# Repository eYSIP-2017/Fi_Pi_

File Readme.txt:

Hello,
This repo contains the documentation and codes of the project 
FiPi- Adapter board development for Firebird V using Raspberry Pi

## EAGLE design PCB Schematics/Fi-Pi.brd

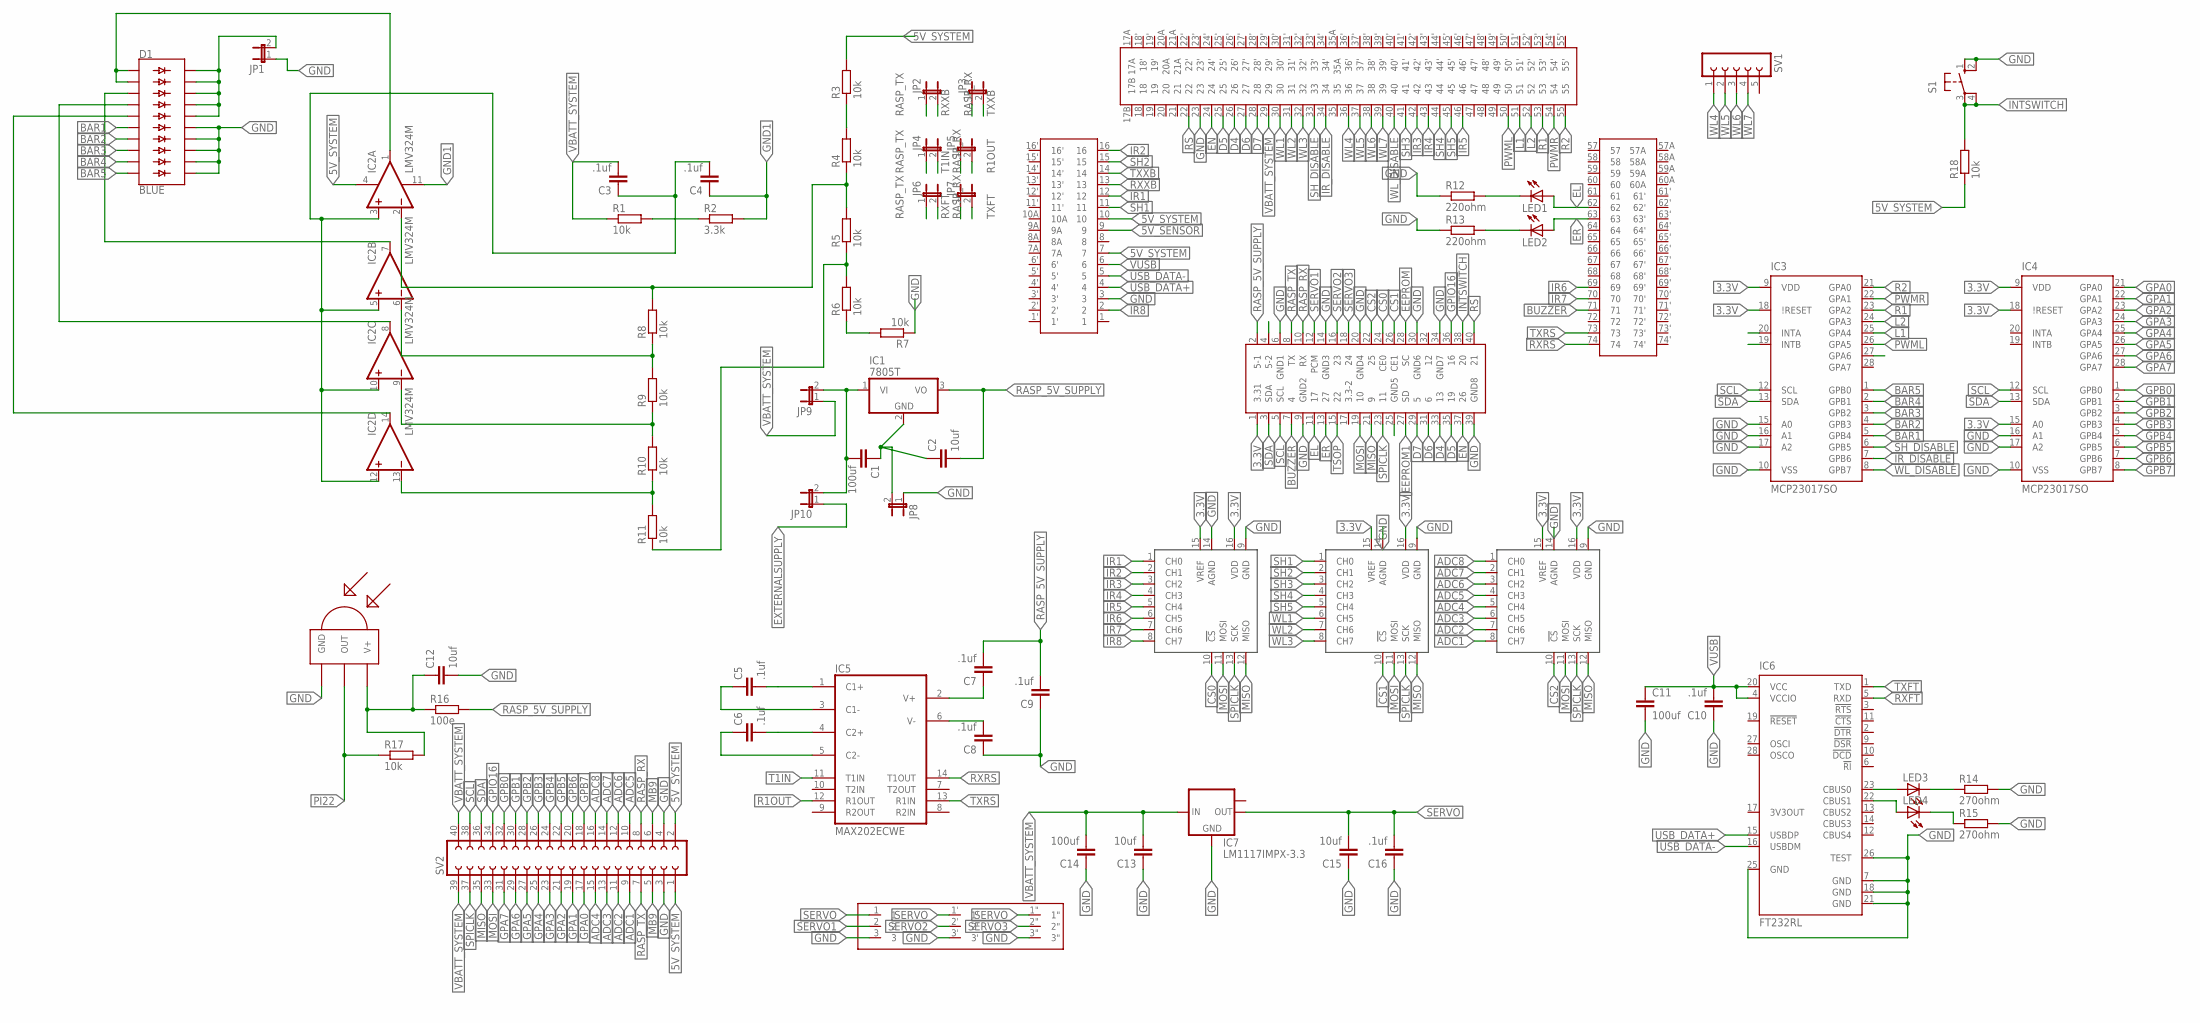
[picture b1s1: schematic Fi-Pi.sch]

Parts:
C1, C11, C14: 100uf; C1206
C2, C12, C13, C15: 10uf; C1206
C3, C4, C5, C6, C7, C8, C9, C10, C16: .1uf; C1206
D1: BLUE; LED_BARGRAPH_10
IC1: 7805T; TO220H
IC2: LMV324M; SO14
IC3, IC4: MCP23017SO; SO28W
IC5: MAX202ECWE; SO16L
IC6: FT232RL; SSOP28
IC7: LM1117IMPX-3.3; SOT223
JP1, JP2, JP3, JP4, JP5, JP6, JP7, JP8, JP9, JP10: JP1E; JP1
LED1, LED2, LED3, LED4: LED_E; LED_1206
R1, R3, R4, R5, R6, R7, R8, R9, R10, R11, R17, R18: 10k; R1206
R2: 3.3k; R1206
R12, R13: 220ohm; R1206
R14, R15: 270ohm; R1206
R16: 100e; R1206
S1: 10-XX; B3F-10XX
SV1: FE05-1
SV2: FE20-2
U$1: DAUGHTERBOARDDAUGHTERBOARD; DAUGHTERBOARD
U$2: MALE_HEADER; MALE_HEADER_PACKAGE
U$3, U$4, U$5: MCP3008SL; SO16
U$6: TSOP1738; TSOP17XX
U$7: SERVO

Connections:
3.3V: IC3.9 (VDD), IC3.18 (\!RESET), IC4.9 (VDD), IC4.15 (A0), IC4.18 (\!RESET), U$2.1 (3.31), U$3.15 (VREF), U$3.16 (VDD), U$4.15 (VREF), U$4.16 (VDD), U$5.15 (VREF), U$5.16 (VDD)
5V_SENSOR: U$1.9
5V_SYSTEM: IC2.4 (V+), R3.2, R18.1, SV2.1, SV2.2, U$1.7, U$1.10
A: D1.16 (C4), D1.17 (C3), D1.18 (C2), D1.19 (C1), D1.20 (C), JP1.2
ADC1: SV2.9, U$5.8 (CH7)
ADC2: SV2.11, U$5.7 (CH6)
ADC3: SV2.13, U$5.6 (CH5)
ADC4: SV2.15, U$5.5 (CH4)
ADC5: SV2.10, U$5.4 (CH3)
ADC6: SV2.12, U$5.3 (CH2)
ADC7: SV2.14, U$5.2 (CH1)
ADC8: SV2.16, U$5.1 (CH0)
BAR1: D1.6 (A5), IC3.5 (GPB4)
BAR2: D1.7 (A6), IC3.4 (GPB3)
BAR3: D1.8 (A7), IC3.3 (GPB2)
BAR4: D1.9 (A8), IC3.2 (GPB1)
BAR5: D1.10 (A9), IC3.1 (GPB0)
BUZZER: U$1.71, U$2.7 (4)
CS0: U$2.24 (CE0), U$3.10 (!CS)
CS1: U$2.26 (CE1), U$4.10 (!CS)
CS2: U$2.22 (25), U$5.10 (!CS)
D4: U$1.26, U$2.33 (13)
D5: U$1.25, U$2.35 (19)
D6: U$1.27, U$2.31 (6)
D7: U$1.28, U$2.29 (5)
EEPROM: U$2.28 (SC)
EEPROM1: U$2.27 (SD)
EL: LED1.A, U$1.62, U$2.11 (17)
EN: U$1.24, U$2.37 (26)
ER: LED2.A, U$1.63, U$2.13 (27)
EXTERNALSUPPLY: JP10.1
GND: C8.1, C9.1, C10.1, C11.2, C12.2, C13.1, C14.1, C15.1, C16.1, D1.11 (C9), D1.12 (C8), D1.13 (C7), D1.14 (C6), D1.15 (C5), IC3.10 (VSS), IC3.15 (A0), IC3.16 (A1), IC3.17 (A2), IC4.10 (VSS), IC4.16 (A1), IC4.17 (A2), IC5.15 (GND), IC6.7 (GND), IC6.18 (GND), IC6.21 (GND), IC6.25 (GND), IC6.26 (TEST), IC7.1 (GND), JP1.1, JP8.1, R7.1, R12.1, R13.1, R14.2, R15.2, S1.1 (S), S1.2 (S1), SV2.3, SV2.4, U$1.3, U$1.23, U$2.6 (GND1), U$2.9 (GND2), U$2.14 (GND3), U$2.20 (GND4), U$2.25 (GND5), U$2.30 (GND6), U$2.34 (GND7), U$2.39 (GND8), U$3.9 (GND), U$3.14 (AGND), U$4.9 (GND), U$4.14 (AGND), U$5.9 (GND), U$5.14 (AGND), U$6.GND, U$7.3, U$7.3", U$7.3'
GND1: C4.1, IC2.11 (V-), R2.2
GPA0: IC4.21 (GPA0), SV2.17
GPA1: IC4.22 (GPA1), SV2.19
GPA2: IC4.23 (GPA2), SV2.21
GPA3: IC4.24 (GPA3), SV2.23
GPA4: IC4.25 (GPA4), SV2.25
GPA5: IC4.26 (GPA5), SV2.27
GPA6: IC4.27 (GPA6), SV2.29
GPA7: IC4.28 (GPA7), SV2.31
GPB0: IC4.1 (GPB0), SV2.32
GPB1: IC4.2 (GPB1), SV2.30
GPB2: IC4.3 (GPB2), SV2.28
GPB3: IC4.4 (GPB3), SV2.26
GPB4: IC4.5 (GPB4), SV2.24
GPB5: IC4.6 (GPB5), SV2.22
GPB6: IC4.7 (GPB6), SV2.20
GPB7: IC4.8 (GPB7), SV2.18
GPIO16: SV2.34, U$2.36 (16)
INTSWITCH: R18.2, S1.3, S1.4 (P1), U$2.38 (20)
IR1: U$1.12, U$3.1 (CH0)
IR2: U$1.16, U$3.2 (CH1)
IR3: U$1.42, U$3.3 (CH2)
IR4: U$1.43, U$3.4 (CH3)
IR5: U$1.46, U$3.5 (CH4)
IR6: U$1.69, U$3.6 (CH5)
IR7: U$1.70, U$3.7 (CH6)
IR8: U$1.2, U$3.8 (CH7)
IR_DISABLE: IC3.7 (GPB6), U$1.34
L1: IC3.25 (GPA4), U$1.51
L2: IC3.24 (GPA3), U$1.52
MB9: SV2.5, SV2.6
MISO: SV2.35, U$2.21 (9), U$3.12 (MISO), U$4.12 (MISO), U$5.12 (MISO)
MOSI: SV2.33, U$2.19 (10), U$3.11 (MOSI), U$4.11 (MOSI), U$5.11 (MOSI)
unnamed: C1.1, C2.1, IC1.2 (GND), JP8.2
unnamed: R5.1, R6.2, R11.1
unnamed: C3.1, C4.2, IC2.3 (+IN), IC2.5 (+IN), IC2.10 (+IN), IC2.12 (+IN), R1.2, R2.1
unnamed: R3.1, R4.2
unnamed: IC2.2 (-IN), R4.1, R5.2, R8.2
unnamed: IC2.6 (-IN), R8.1, R9.2
unnamed: R6.1, R7.2
unnamed: IC2.9 (-IN), R9.1, R10.2
unnamed: IC2.13 (-IN), R10.1, R11.2
unnamed: D1.1 (A), D1.2 (A1), IC2.1 (OUT)
unnamed: C5.1, IC5.3 (C1-)
unnamed: D1.4 (A3), IC2.8 (OUT)
unnamed: D1.5 (A4), IC2.14 (OUT)
unnamed: LED1.C, R12.2
unnamed: LED2.C, R13.2
unnamed: C5.2, IC5.1 (C1+)
unnamed: C6.2, IC5.4 (C2+)
unnamed: C6.1, IC5.5 (C2-)
unnamed: LED4.C, R15.1
unnamed: D1.3 (A2), IC2.7 (OUT)
unnamed: LED3.C, R14.1
unnamed: IC6.23 (CBUS0), LED3.A
unnamed: IC6.22 (CBUS1), LED4.A
unnamed: C7.1, IC5.2 (V+)
unnamed: C8.2, IC5.6 (V-)
unnamed: C12.1, R16.1, R17.2, U$6.V+
PI4: U$2.4 (5-2)
PI22: R17.1, U$6.OUT
PWML: IC3.26 (GPA5), U$1.50
PWMR: IC3.22 (GPA1), U$1.54
R1: IC3.23 (GPA2), U$1.53
R1OUT: IC5.12 (R1OUT), JP5.2
R2: IC3.21 (GPA0), U$1.55
RASP_5V_SUPPLY: C2.2, C7.2, C9.2, IC1.3 (VO), R16.2, U$2.2 (5-1)
RASP_RX: JP3.1, JP5.1, JP7.1, SV2.8, U$2.10 (RX)
RASP_TX: JP2.1, JP4.1, JP6.1, SV2.7, U$2.8 (TX)
RS: U$1.22, U$2.40 (21)
RXFT: IC6.5 (RXD), JP6.2
RXRS: IC5.14 (T1OUT), U$1.74
RXXB: JP2.2, U$1.13
SCL: IC3.12 (SCL), IC4.12 (SCL), SV2.38, U$2.5 (SCL)
SDA: IC3.13 (SDA), IC4.13 (SDA), SV2.36, U$2.3 (SDA)
SERVO: C15.2, C16.2, IC7.2 (OUT), U$7.1, U$7.1", U$7.1'
SERVO1: U$2.12 (PCM), U$7.2
SERVO2: U$2.16 (23), U$7.2'
SERVO3: U$2.18 (24), U$7.2"
SH1: U$1.11, U$4.1 (CH0)
SH2: U$1.15, U$4.2 (CH1)
SH3: U$1.41, U$4.3 (CH2)
SH4: U$1.44, U$4.4 (CH3)
SH5: U$1.45, U$4.5 (CH4)
SH_DISABLE: IC3.6 (GPB5), U$1.33
SPICLK: SV2.37, U$2.23 (11), U$3.13 (SCK), U$4.13 (SCK), U$5.13 (SCK)
T1IN: IC5.11 (T1IN), JP4.2
TSOP: U$2.15 (22)
TXFT: IC6.1 (TXD), JP7.2
TXRS: IC5.13 (R1IN), U$1.73
TXXB: JP3.2, U$1.14
USB_DATA+: IC6.15 (USBDP), U$1.4
USB_DATA-: IC6.16 (USBDM), U$1.5
VBATT_SYSTEM: C1.2, C3.2, C13.2, C14.2, IC1.1 (VI), IC7.3 (IN), JP9.1, JP9.2, JP10.2, R1.1, SV2.39, SV2.40, U$1.29
VCC: IC5.16 (VCC)
VUSB: C10.2, C11.1, IC6.4 (VCCIO), IC6.20 (VCC), U$1.6
WL1: U$1.30, U$4.6 (CH5)
WL2: U$1.31, U$4.7 (CH6)
WL3: U$1.32, U$4.8 (CH7)
WL4: SV1.1, U$1.36
WL5: SV1.2, U$1.37
WL6: SV1.3, U$1.38
WL7: SV1.4, U$1.39
WL_DISABLE: IC3.8 (GPB7), U$1.40

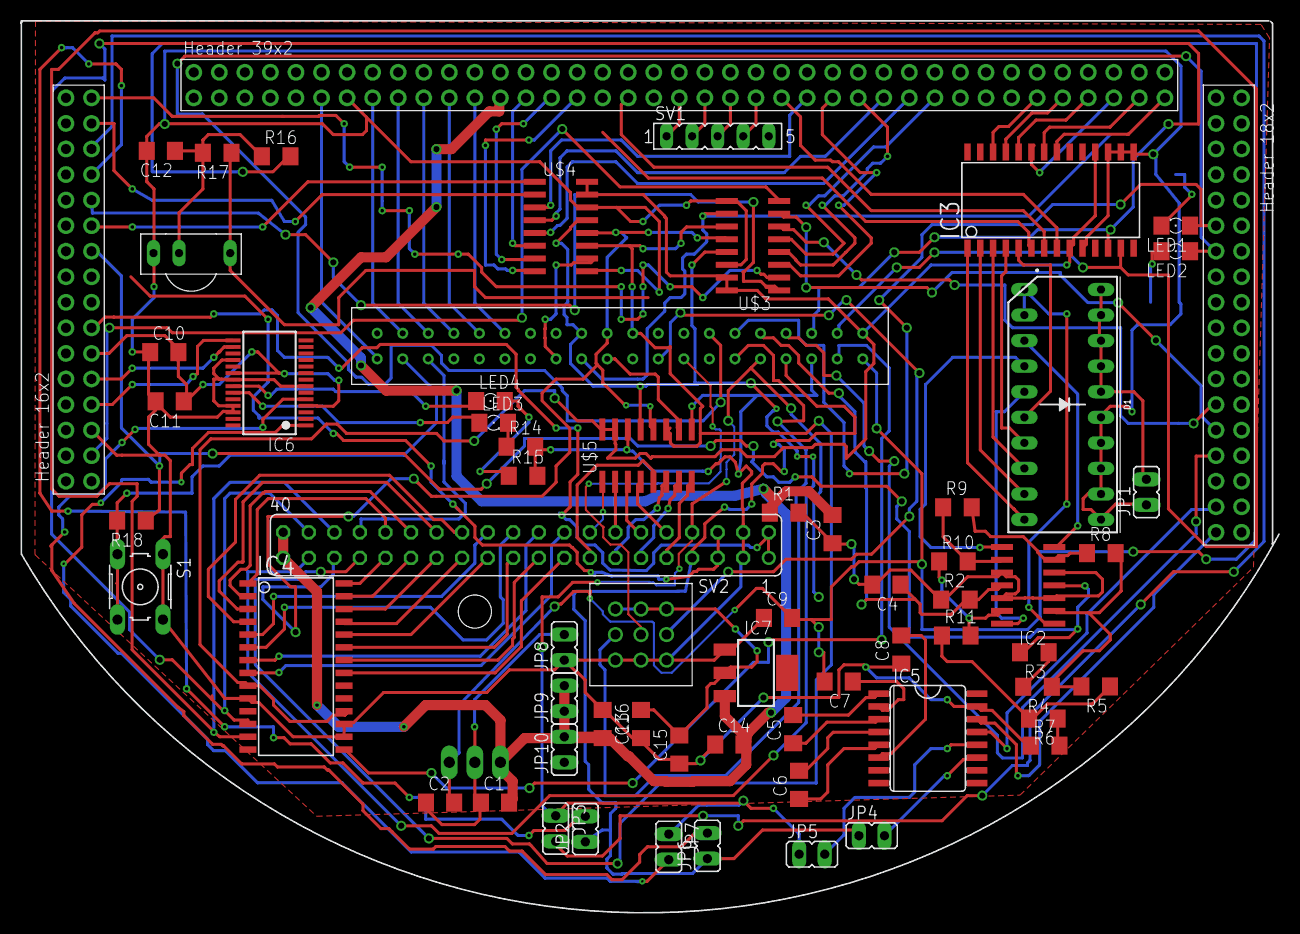
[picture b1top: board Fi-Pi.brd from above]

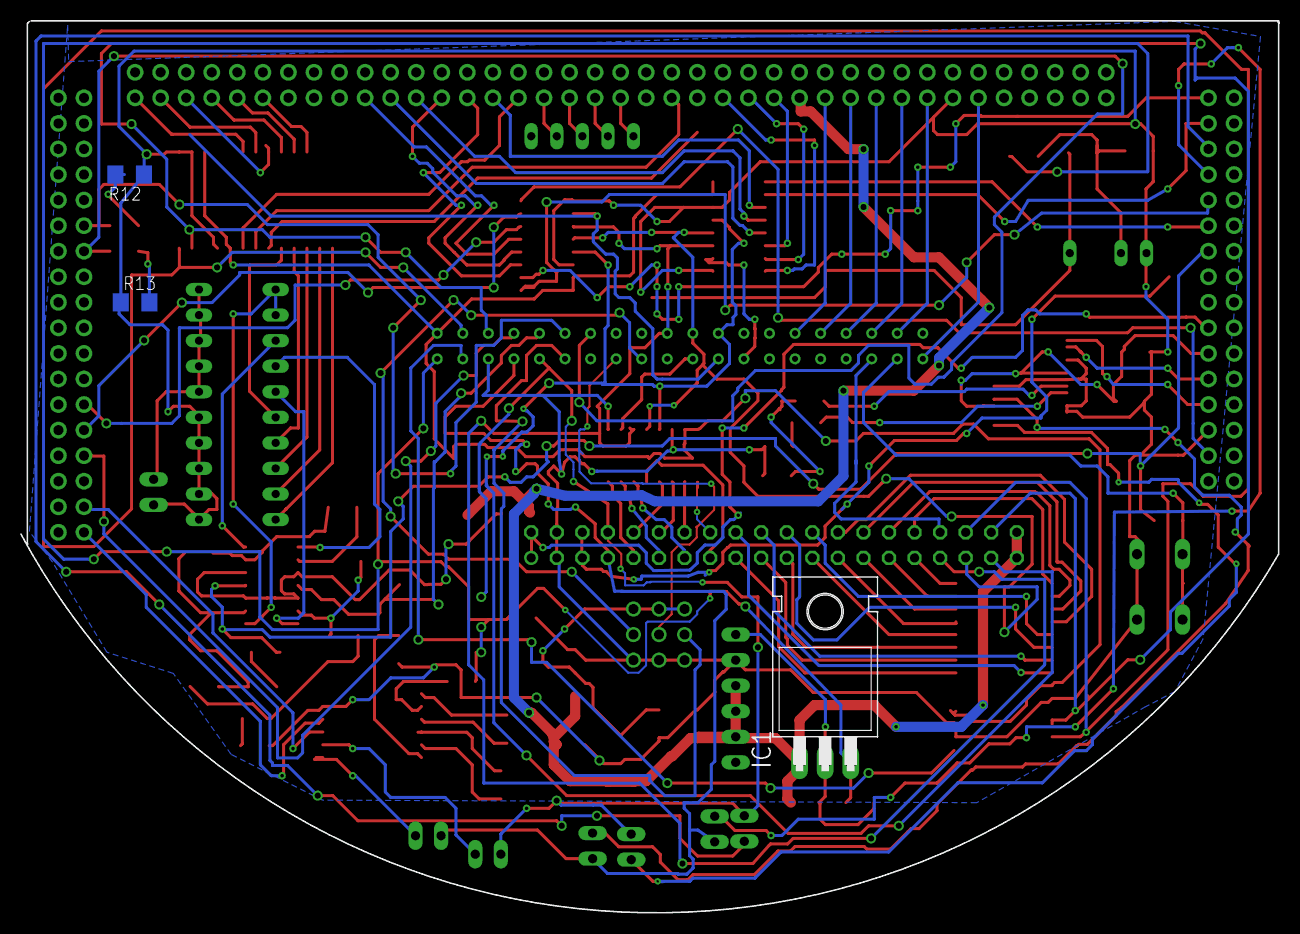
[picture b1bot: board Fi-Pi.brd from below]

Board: 2 copper layers, 125.1 x 88.6 mm, 66 parts (3 on the bottom side), 129 nets.

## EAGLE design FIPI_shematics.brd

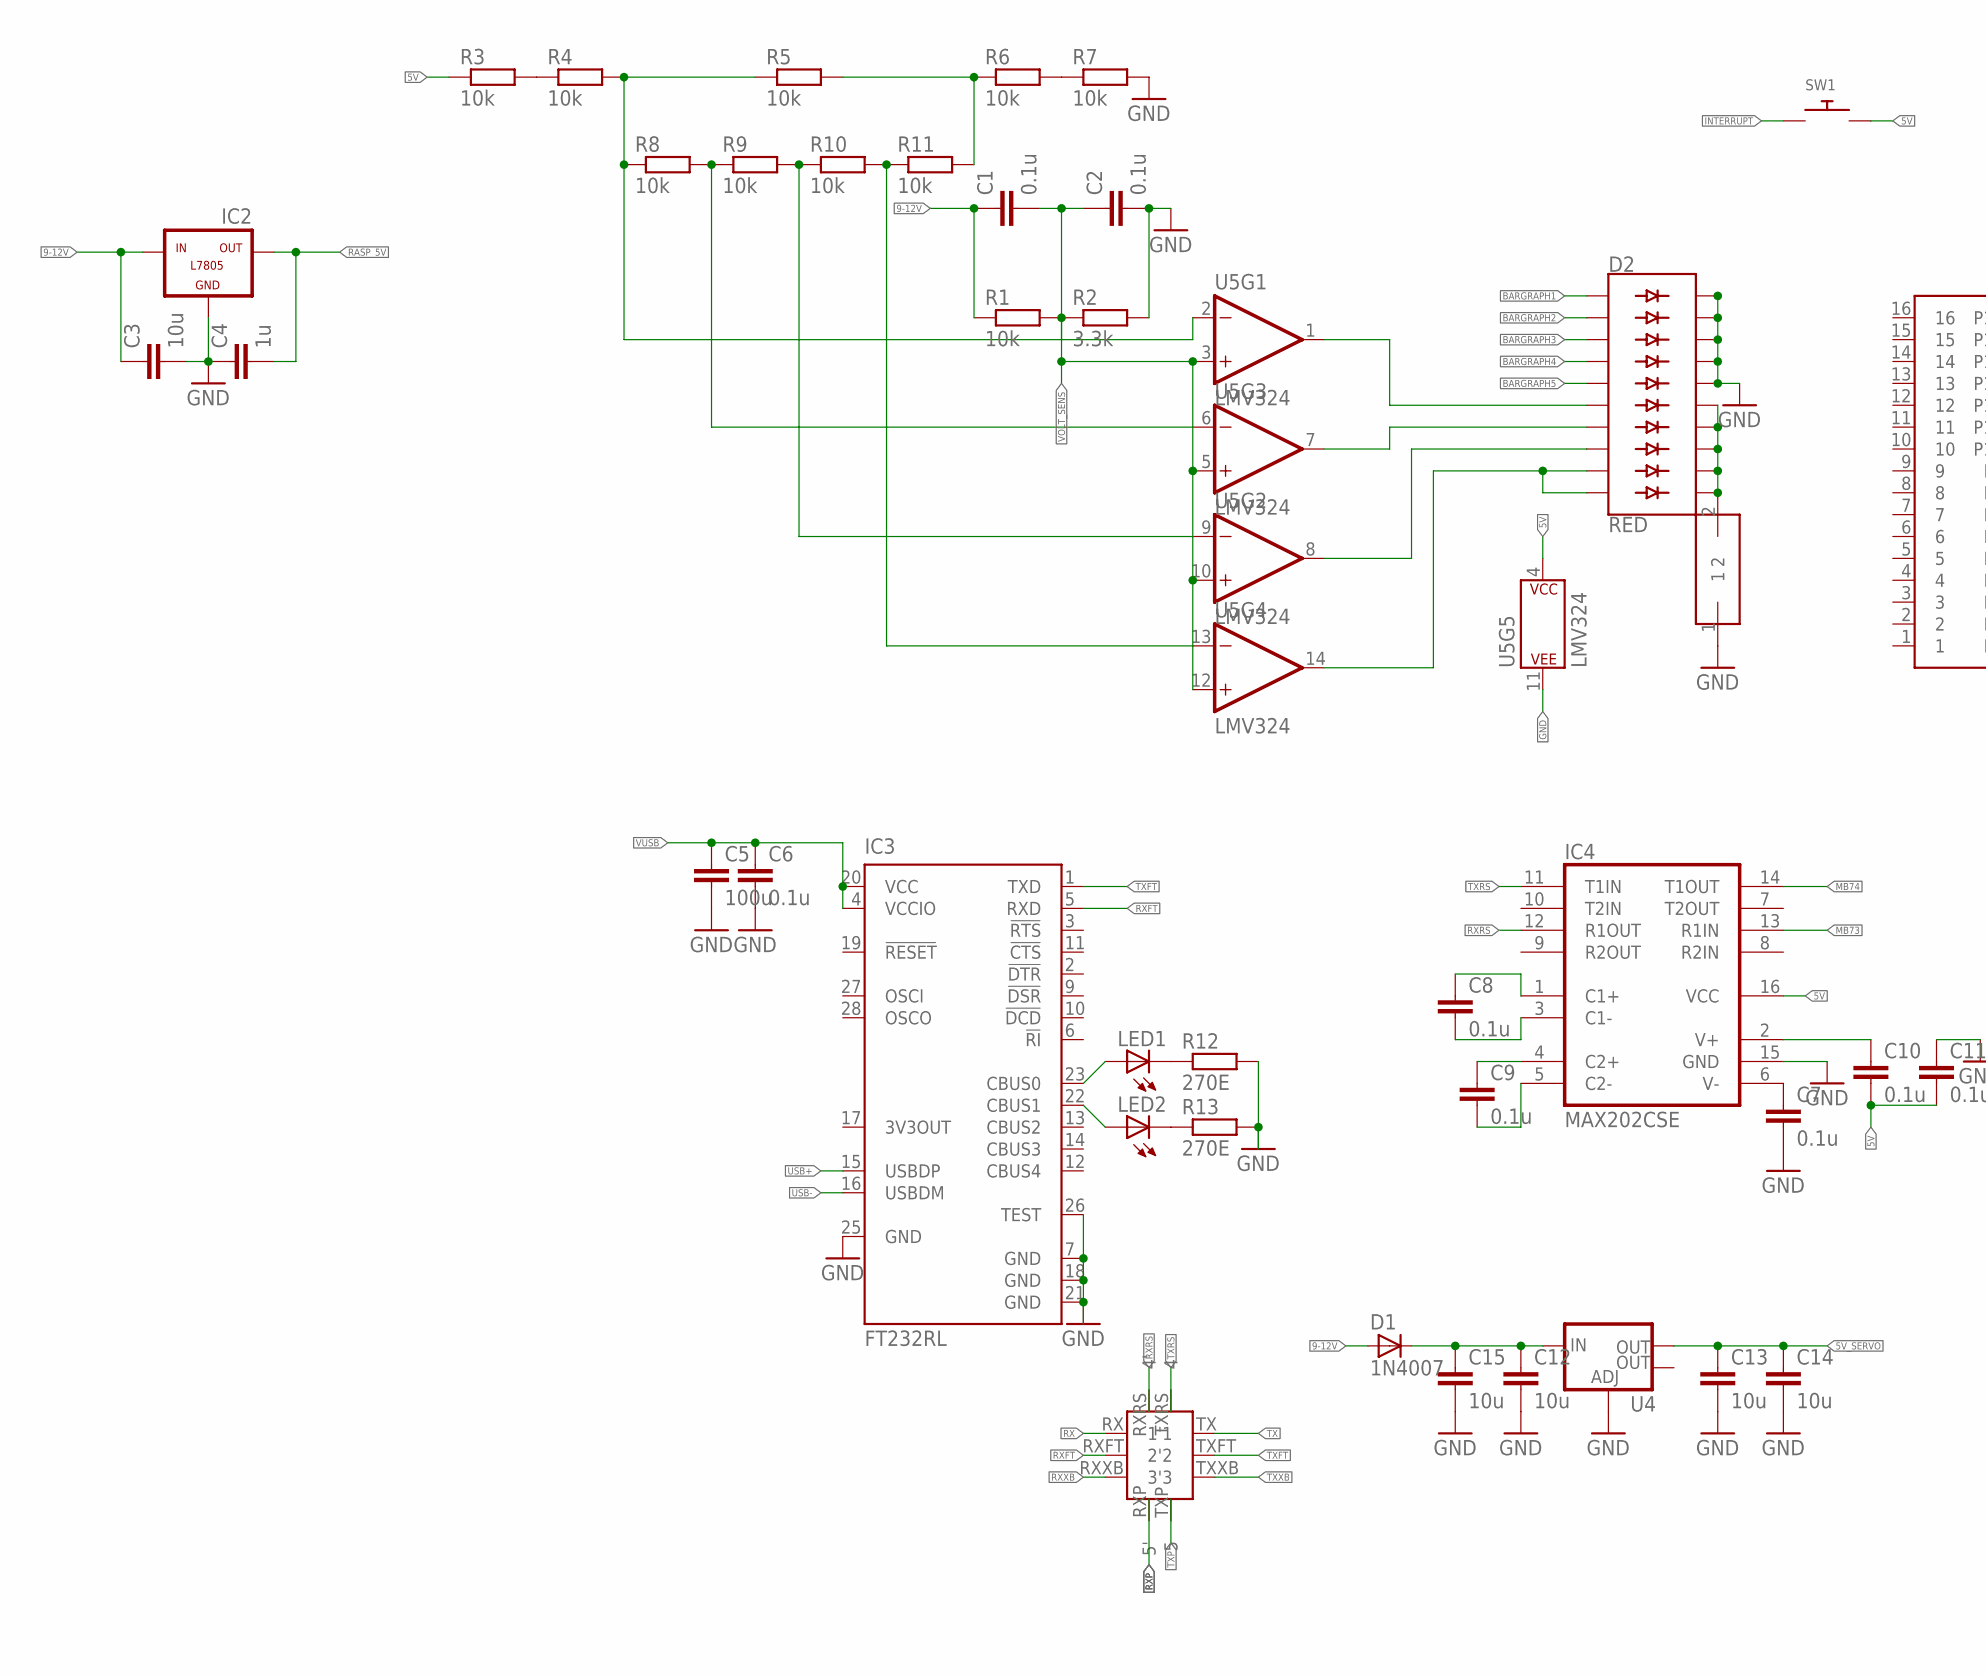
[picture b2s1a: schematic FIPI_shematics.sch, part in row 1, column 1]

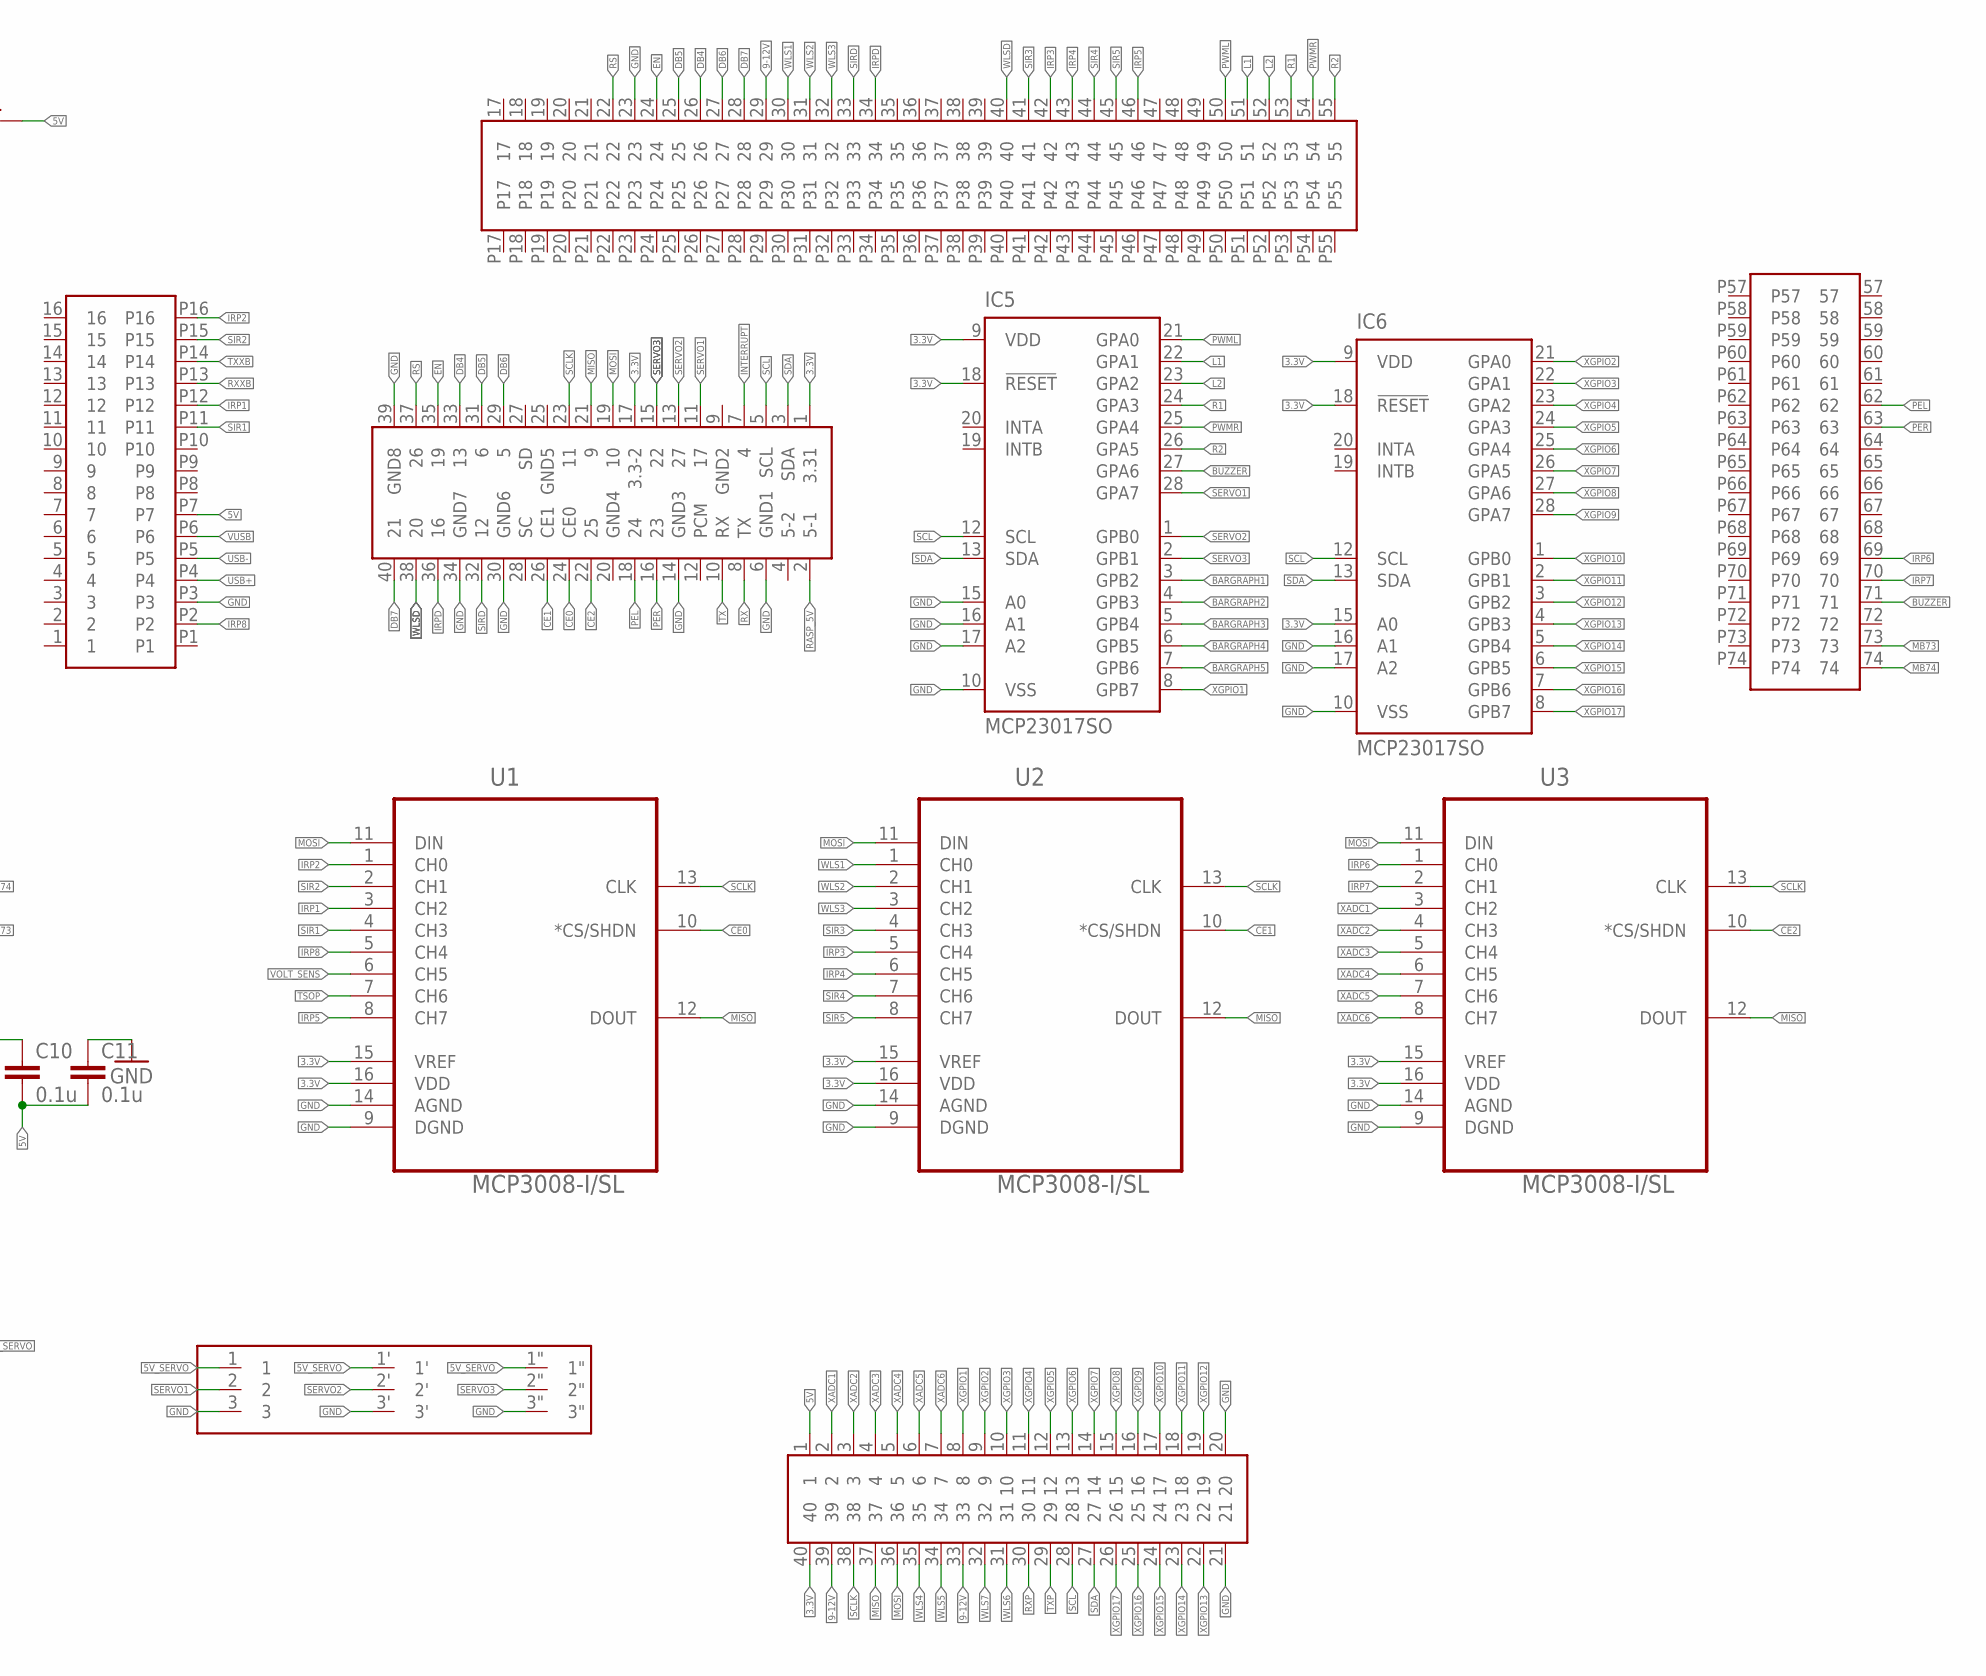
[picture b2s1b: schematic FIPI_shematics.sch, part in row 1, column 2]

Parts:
C1, C2, C6, C7, C8, C9, C10, C11: 0.1u; C1206
C3, C12, C13, C14, C15: 10u; C1206
C4: 1u; C1206
C5: 100u; C1206
D1: 1N4007; SMA
D2: RED; LED_BARGRAPH_10
IC2: L7805; 78XXL
IC3: FT232RL; SSOP28
IC4: MAX202CSE; SO16
IC5, IC6: MCP23017SO; SO28W
LED1, LED2: LED_E; LED_1206
R1, R3, R4, R5, R6, R7, R8, R9, R10, R11: 10k; M1206
R2: 3.3k; M1206
R12, R13: 270E; R1206
RASPPI: MALE_HEADER; MALE_HEADER_PACKAGE
SW1: SWITCH_PUSHBUTTONSOFTTOUCHSMD_SJ; PUSHBUTTON_SMD_SJ
U1, U2, U3: MCP3008-I/SL; SOIC127P600X175-16N
U4: V_REG_LM1117SOT223; SOT223
U5: LMV324; SO14
U$1: BOARD; FEMHEADER
U$3: SWITCH_RXTX
U$4: SWITCH1
U$5: PORT_EXP
U$7: SERVO

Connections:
3.3V: IC5.9 (VDD), IC5.18 (!RESET), IC6.9 (VDD), IC6.15 (A0), IC6.18 (!RESET), RASPPI.1 (3.31), RASPPI.17 (3.3-2), U1.15 (VREF), U1.16 (VDD), U2.15 (VREF), U2.16 (VDD), U3.15 (VREF), U3.16 (VDD), U$5.40
5V: C10.2, C11.2, IC4.16 (VCC), R3.1, SW1.P$2, U5.4 (P$V+), U$1.P7, U$5.1
5V_SERVO: C13.1, C14.1, U4.2 (OUT), U$7.1, U$7.1", U$7.1'
9-12V: C1.1, C3.1, D1.A, IC2.IN, R1.1, U$1.29, U$5.33, U$5.39
BARGRAPH1: D2.1 (A), IC5.3 (GPB2)
BARGRAPH2: D2.2 (A1), IC5.4 (GPB3)
BARGRAPH3: D2.3 (A2), IC5.5 (GPB4)
BARGRAPH4: D2.4 (A3), IC5.6 (GPB5)
BARGRAPH5: D2.5 (A4), IC5.7 (GPB6)
BUZZER: IC5.27 (GPA6), U$1.71
CE0: RASPPI.24 (CE0), U1.10 (*CS/SHDN)
CE1: RASPPI.26 (CE1), U2.10 (*CS/SHDN)
CE2: RASPPI.22 (25), U3.10 (*CS/SHDN)
DB4: RASPPI.33 (13), U$1.26
DB5: RASPPI.31 (6), U$1.25
DB6: RASPPI.29 (5), U$1.27
DB7: RASPPI.40 (21), U$1.28
EN: RASPPI.35 (19), U$1.24
GND: C2.2, C3.2, C4.1, C5.2, C6.2, C7.2, C11.1, C12.2, C13.2, C14.2, C15.2, D2.16 (C4), D2.17 (C3), D2.18 (C2), D2.19 (C1), D2.20 (C), IC2.GND, IC3.7 (GND), IC3.18 (GND), IC3.21 (GND), IC3.25 (GND), IC3.26 (TEST), IC4.15 (GND), IC5.10 (VSS), IC5.15 (A0), IC5.16 (A1), IC5.17 (A2), IC6.10 (VSS), IC6.16 (A1), IC6.17 (A2), R2.2, R7.2, R12.2, R13.2, RASPPI.6 (GND1), RASPPI.14 (GND3), RASPPI.30 (GND6), RASPPI.34 (GND7), RASPPI.39 (GND8), U1.9 (DGND), U1.14 (AGND), U2.9 (DGND), U2.14 (AGND), U3.9 (DGND), U3.14 (AGND), U4.1 (ADJ), U5.11 (P$V-), U$1.23, U$1.P3, U$4.1, U$5.20, U$5.21, U$7.3, U$7.3", U$7.3'
INTERRUPT: RASPPI.7 (4), SW1.P$1
IRP1: U1.3 (CH2), U$1.P12
IRP2: U1.1 (CH0), U$1.P16
IRP3: U2.5 (CH4), U$1.42
IRP4: U2.6 (CH5), U$1.43
IRP5: U1.8 (CH7), U$1.46
IRP6: U3.1 (CH0), U$1.69
IRP7: U3.2 (CH1), U$1.70
IRP8: U1.5 (CH4), U$1.P2
IRPD: RASPPI.36 (16), U$1.34
L1: IC5.22 (GPA1), U$1.51
L2: IC5.23 (GPA2), U$1.52
MB73: IC4.13 (R1IN), U$1.73
MB74: IC4.14 (T1OUT), U$1.74
MISO: RASPPI.21 (9), U1.12 (DOUT), U2.12 (DOUT), U3.12 (DOUT), U$5.37
MOSI: RASPPI.19 (10), U1.11 (DIN), U2.11 (DIN), U3.11 (DIN), U$5.36
unnamed: R3.2, R4.1
unnamed: C12.1, C15.1, D1.K (C), U4.3 (IN)
unnamed: R4.2, R5.1, R8.1, U5.2 (-IN)
unnamed: R5.2, R6.1, R11.2
unnamed: R6.2, R7.1
unnamed: R8.2, R9.1, U5.6 (-IN)
unnamed: R9.2, R10.1, U5.9 (-IN)
unnamed: R10.2, R11.1, U5.13 (-IN)
unnamed: D2.11 (C9), D2.12 (C8), D2.13 (C7), D2.14 (C6), D2.15 (C5), U$4.2
unnamed: D2.9 (A8), D2.10 (A9), U5.14 (OUT)
unnamed: D2.8 (A7), U5.8 (OUT)
unnamed: D2.7 (A6), U5.7 (OUT)
unnamed: D2.6 (A5), U5.1 (OUT)
unnamed: C8.1, IC4.1 (C1+)
unnamed: C8.2, IC4.3 (C1-)
unnamed: C9.1, IC4.4 (C2+)
unnamed: C9.2, IC4.5 (C2-)
unnamed: IC3.23 (CBUS0), LED1.A
unnamed: IC3.22 (CBUS1), LED2.A
unnamed: LED1.C, R12.1
unnamed: LED2.C, R13.1
PEL: RASPPI.18 (24), U$1.62
PER: RASPPI.16 (23), U$1.63
PWML: IC5.21 (GPA0), U$1.50
PWMR: IC5.25 (GPA4), U$1.54
R1: IC5.24 (GPA3), U$1.53
R2: IC5.26 (GPA5), U$1.55
RASP_5V: C4.2, IC2.OUT, RASPPI.2 (5-1)
RS: RASPPI.37 (26), U$1.22
RX: RASPPI.8 (TX), U$3.RX (1')
RXFT: IC3.5 (RXD), U$3.RXFT (2')
RXP: U$3.RXP (5'), U$5.30
RXRS: IC4.12 (R1OUT), U$3.RXRS (4')
RXXB: U$1.P13, U$3.RXXB (3')
SCL: IC5.12 (SCL), IC6.12 (SCL), RASPPI.5 (SCL), U$5.28
SCLK: RASPPI.23 (11), U1.13 (CLK), U2.13 (CLK), U3.13 (CLK), U$5.38
SDA: IC5.13 (SDA), IC6.13 (SDA), RASPPI.3 (SDA), U$5.27
SERVO1: IC5.28 (GPA7), RASPPI.11 (17), U$7.2
SERVO2: IC5.1 (GPB0), RASPPI.13 (27), U$7.2'
SERVO3: IC5.2 (GPB1), RASPPI.15 (22), U$7.2"
SIR1: U1.4 (CH3), U$1.P11
SIR2: U1.2 (CH1), U$1.P15
SIR3: U2.4 (CH3), U$1.41
SIR4: U2.7 (CH6), U$1.44
SIR5: U2.8 (CH7), U$1.45
SIRD: RASPPI.32 (12), U$1.33
TSOP: U1.7 (CH6)
TX: RASPPI.10 (RX), U$3.TX (1)
TXFT: IC3.1 (TXD), U$3.TXFT (2)
TXP: U$3.TXP (5), U$5.29
TXRS: IC4.11 (T1IN), U$3.TXRS (4)
TXXB: U$1.P14, U$3.TXXB (3)
USB+: IC3.15 (USBDP), U$1.P4
USB-: IC3.16 (USBDM), U$1.P5
V+: C10.1, IC4.2 (V+)
V-: C7.1, IC4.6 (V-)
VOLT_SENS: C1.2, C2.1, R1.2, R2.1, U1.6 (CH5), U5.3 (+IN), U5.5 (+IN), U5.10 (+IN), U5.12 (+IN)
VUSB: C5.1, C6.1, IC3.4 (VCCIO), IC3.20 (VCC), U$1.P6
WLS1: U2.1 (CH0), U$1.30
WLS2: U2.2 (CH1), U$1.31
WLS3: U2.3 (CH2), U$1.32
WLS4: U$5.35
WLS5: U$5.34
WLS6: U$5.31
WLS7: U$5.32
WLSD: RASPPI.38 (20), U$1.40
XADC1: U3.3 (CH2), U$5.2
XADC2: U3.4 (CH3), U$5.3
XADC3: U3.5 (CH4), U$5.4
XADC4: U3.6 (CH5), U$5.5
XADC5: U3.7 (CH6), U$5.6
XADC6: U3.8 (CH7), U$5.7
XGPIO1: IC5.8 (GPB7), U$5.8
XGPIO2: IC6.21 (GPA0), U$5.9
XGPIO3: IC6.22 (GPA1), U$5.10
XGPIO4: IC6.23 (GPA2), U$5.11
XGPIO5: IC6.24 (GPA3), U$5.12
XGPIO6: IC6.25 (GPA4), U$5.13
XGPIO7: IC6.26 (GPA5), U$5.14
XGPIO8: IC6.27 (GPA6), U$5.15
XGPIO9: IC6.28 (GPA7), U$5.16
XGPIO10: IC6.1 (GPB0), U$5.17
XGPIO11: IC6.2 (GPB1), U$5.18
XGPIO12: IC6.3 (GPB2), U$5.19
XGPIO13: IC6.4 (GPB3), U$5.22
XGPIO14: IC6.5 (GPB4), U$5.23
XGPIO15: IC6.6 (GPB5), U$5.24
XGPIO16: IC6.7 (GPB6), U$5.25
XGPIO17: IC6.8 (GPB7), U$5.26

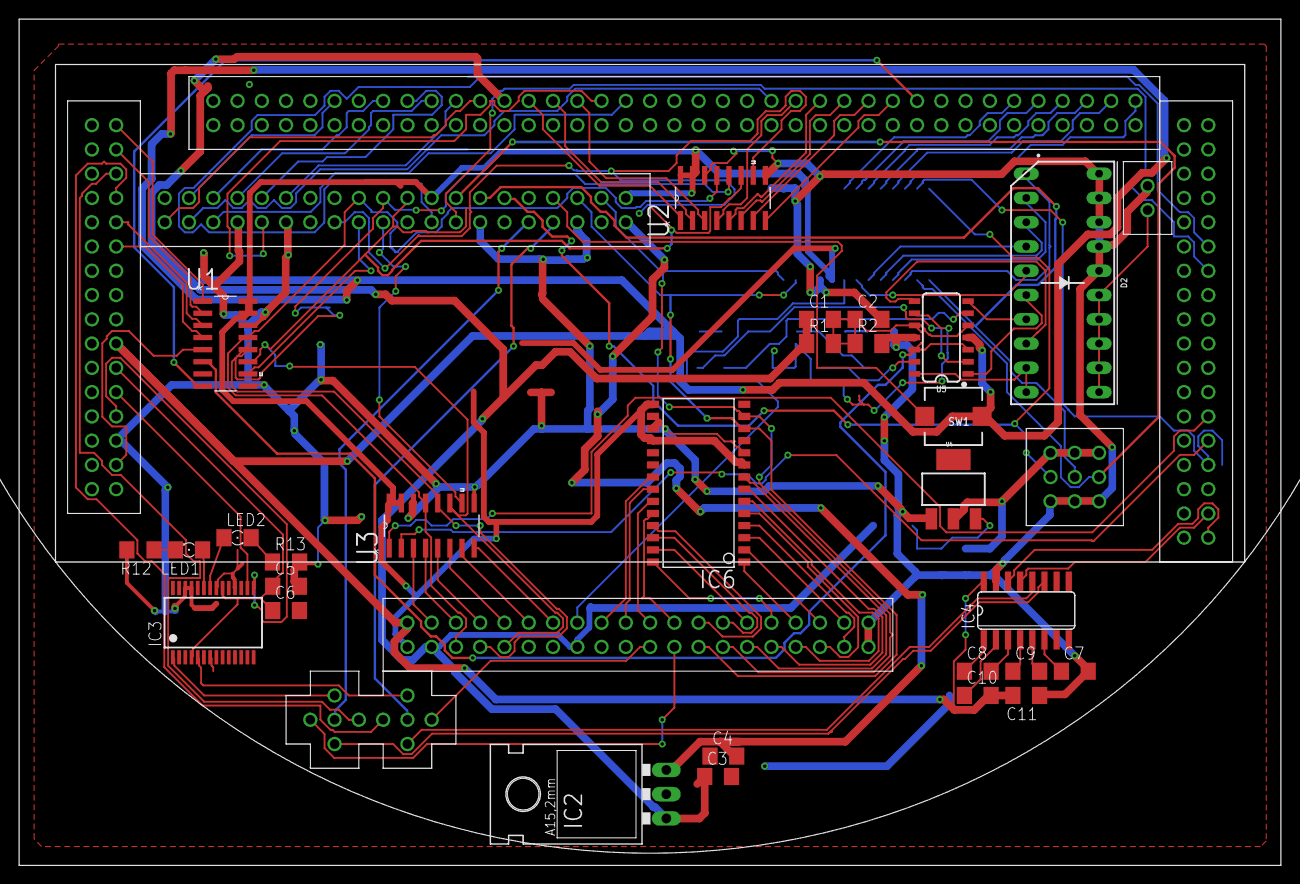
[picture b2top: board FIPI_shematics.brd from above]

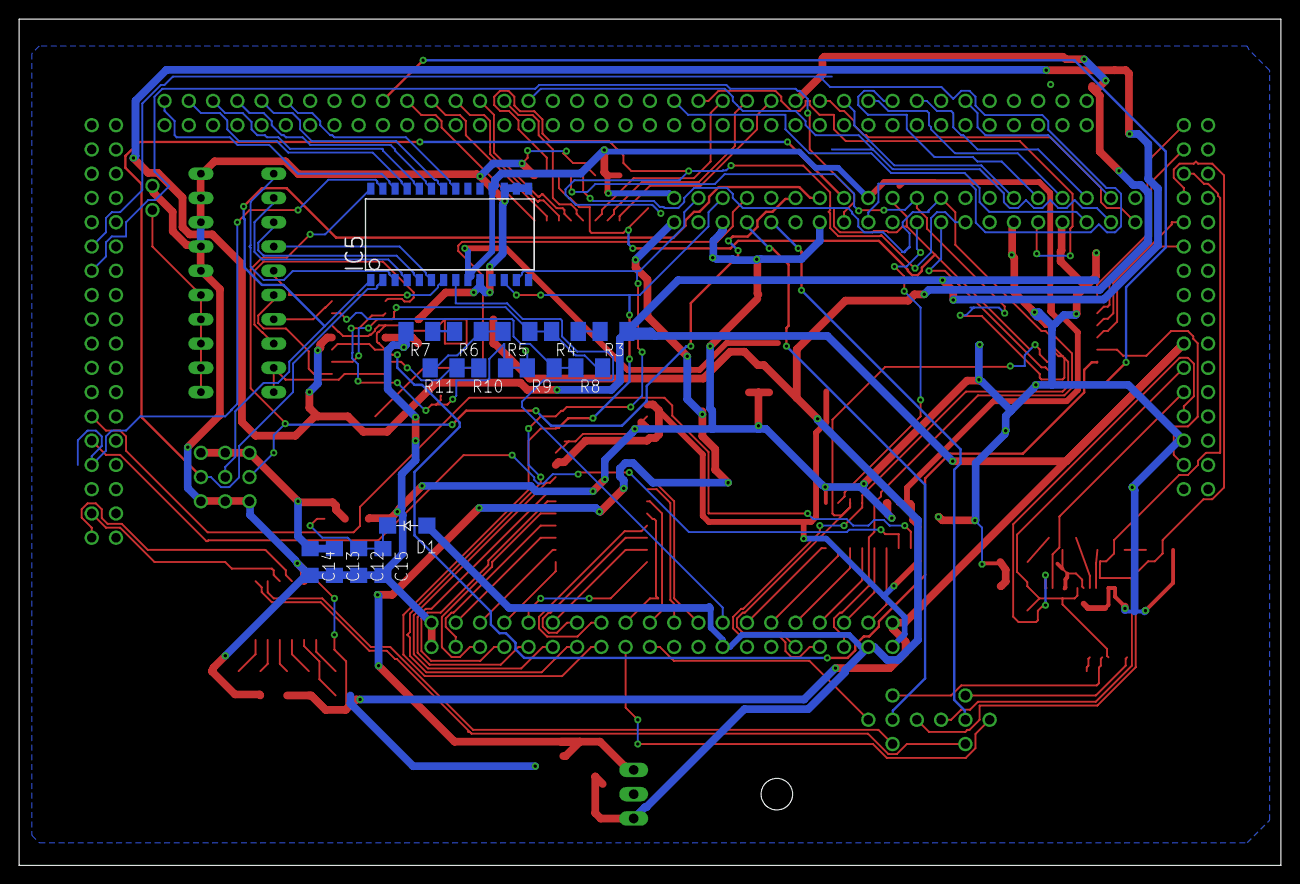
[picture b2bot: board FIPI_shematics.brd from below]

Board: 2 copper layers, 132.1 x 88.6 mm, 49 parts (15 on the bottom side), 119 nets.

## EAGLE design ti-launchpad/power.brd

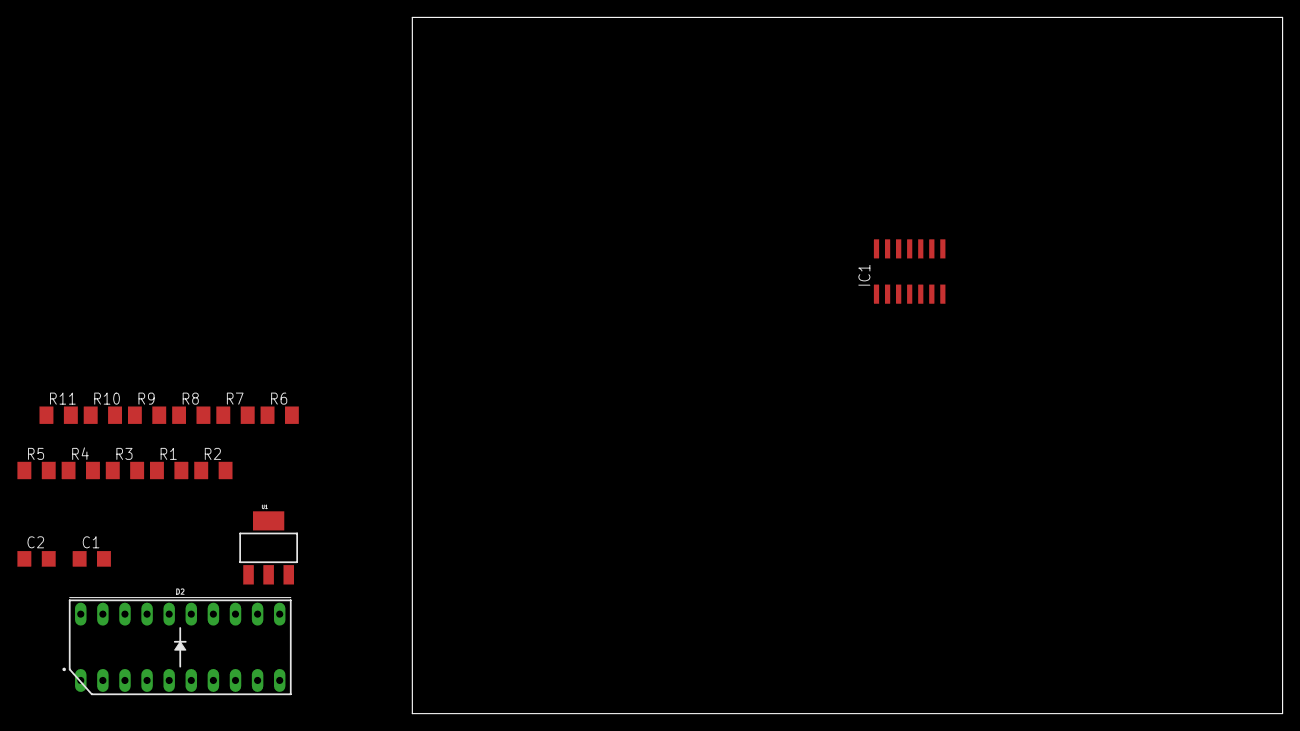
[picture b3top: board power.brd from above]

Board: 2 copper layers, 100.0 x 80.0 mm, 16 parts (0 on the bottom side), 14 nets, no tracks yet.

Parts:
C1, C2: 0.1u; C1206
D2: RED; LED_BARGRAPH_10
IC1: LM324D; SO14
R1, R3, R4, R5, R6, R7, R8, R9, R10, R11: 10k; M1206
R2: 3.3k; M1206
U1: SOT223

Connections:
GND: C2.2, D2.11, D2.12, D2.13, D2.14, D2.15, D2.16, D2.17, D2.18, D2.19, D2.20, R2.2, R7.2
unnamed: R3.2, R4.1
unnamed: C1.2, C2.1, IC1.3, IC1.5, IC1.10, IC1.12, R1.2, R2.1
unnamed: IC1.2, R4.2, R5.1, R8.1
unnamed: R5.2, R6.1, R11.2
unnamed: R6.2, R7.1
unnamed: IC1.6, R8.2, R9.1
unnamed: IC1.9, R9.2, R10.1
unnamed: IC1.13, R10.2, R11.1
unnamed: D2.1, D2.2, D2.3, IC1.1
unnamed: D2.4, D2.5, D2.6, IC1.7
unnamed: D2.7, D2.8, IC1.8
unnamed: D2.9, D2.10, IC1.14
VCC: C1.1, R1.1, R3.1

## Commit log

2017-06-06 Added Buzzer Program
2017-06-06 Added ADC Program
2017-06-06 Added pwm_motot_control
2017-06-06 Added wheel_encoder
2017-06-06 Added LCD
2017-06-06 Added port expander
2017-06-06 Added position encoder program with threads
2017-06-06 Added Xbee program with threads
2017-06-06 Added read_me file
2017-06-06 Added PPT
2017-06-12 eagle backup
2017-06-26 FIPI_schematics
2017-06-26 progress_ppt
2017-06-27 adding files
2017-06-29 added poster
2017-06-29 added poster_update
2017-07-05 added hardware manual
2017-07-05 added changes
2017-07-07 added report

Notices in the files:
parts and their libraries:
SparkFun-LED: Licensing: Creative Commons ShareAlike 4.0 International - https://creativecommons.org/licenses/by-sa/4.0
